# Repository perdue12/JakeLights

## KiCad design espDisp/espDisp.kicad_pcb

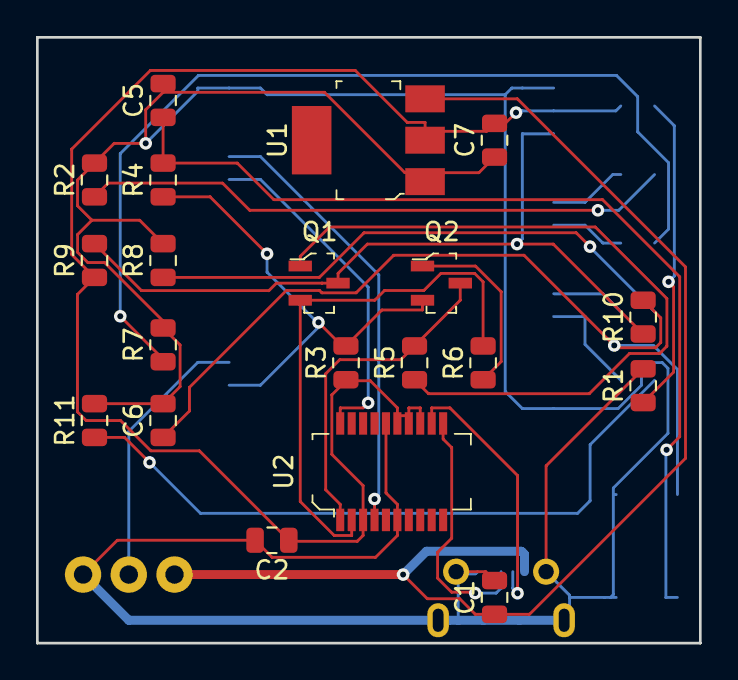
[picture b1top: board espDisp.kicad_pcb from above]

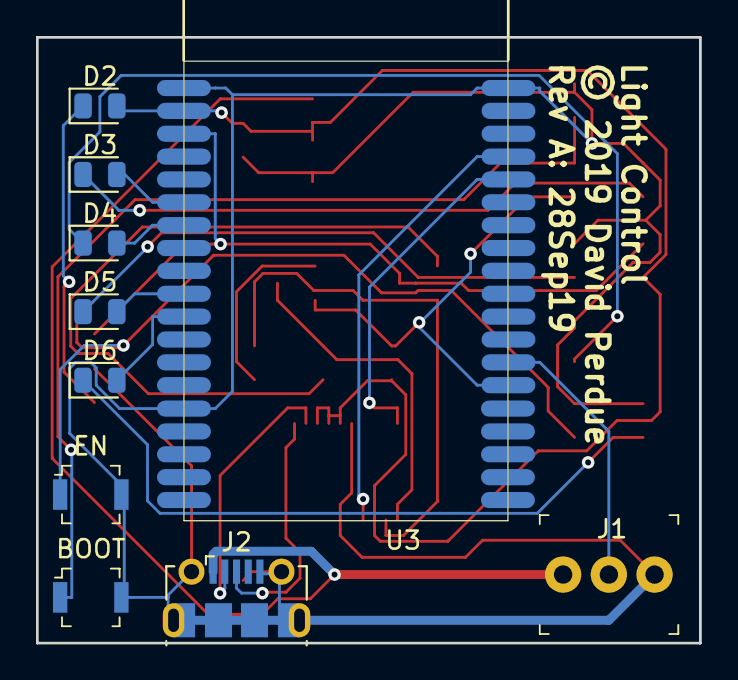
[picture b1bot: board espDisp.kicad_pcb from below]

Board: 2 copper layers, 36.8 x 33.7 mm, 30 parts (10 on the bottom side), 25 nets.

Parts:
BOOT: BOOT; Switch_Tactile_SMD_B3U-1000P
C1, C2, C5, C6: 1.0u; C_0805_2012Metric
C7: 47u; C_0805_2012Metric
D2, D3, D4, D5, D6: LED; LED_0805_2012Metric
EN: EN; Switch_Tactile_SMD_B3U-1000P
J1: 0022232031; PinHeader_1x3_P2.54mm_Drill1.02mm
J2: USB_B_Micro; USB_Micro-B_Molex-105017-0001
Q1, Q2: BC817-25-TP; SOT-23-3
R1, R2, R7, R8, R11: 200; R_0805_2012Metric
R3, R4, R9, R10: 1K; R_0805_2012Metric
R5, R6: 10K; R_0805_2012Metric
U1: AZ1117CH-3_3TRG1; SOT-223
U2: FT231XS-U; SSOP-20_W3.9mm
U3: ESP32-WROVER

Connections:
340RX: U2.4, U3.35
340TX: U2.20, U3.34
+3V3: C2.1, C7.2, D2.2, R3.1, R9.1, U1.2, U2.3, U2.13, U2.14, U2.15, U3.2
+5V: C1.1, J1.1, J2.1, U1.3
DTR: Q2.3, R5.2, U2.1
EN: Q1.3, R9.2, R10.1, U3.3
GND: BOOT.2, C1.2, C2.2, C5.2, C6.2, C7.1, EN.2, J1.3, J2.5, J2.6, R1.2, R2.2, R7.2, R8.2, R11.2, U1.1, U2.6, U2.16, U3.1, U3.15, U3.38
IO0: Q2.2, R3.2, R4.1, U3.25
LED1: D3.2, U3.6
LED2: D4.2, U3.7
LED3: D5.2, U3.10
LED4: D6.2, U3.11
LED_Din: J1.2, U3.26
unnamed: BOOT.1, C5.1, R4.2
unnamed: C6.1, EN.1, R10.2
unnamed: D2.1, R1.1
unnamed: D3.1, R2.1
unnamed: D4.1, R7.1
unnamed: D5.1, R8.1
unnamed: D6.1, R11.1
unnamed: Q1.1, R5.1
unnamed: Q2.1, R6.1
RTS: Q1.2, R6.2, U2.2
USB_D+: J2.3, U2.11
USB_D-: J2.2, U2.12

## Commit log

2019-08-18 Initlal commit
2019-08-18 before trying json
2019-08-18 reflashing
2019-08-18 fixed readme
2019-08-19 About to go asyncio
2019-08-25 add spiram
2019-08-25 seperated main and boot
2019-08-25 Don't redefin the pins you are using for i2c comms
2019-08-25 added regex
2019-08-25 web api, and set light function working
2019-08-25 made led array 1 based.
2019-08-27 changed to proper logging
2019-08-28 added newer roms
2019-08-28 removed oled
2019-09-01 changed to tinyweb
2019-09-01 remove led from boot
2019-09-02 Working json and async
2019-09-02 removed some prints
2019-09-02 set dhcp hostname
2019-09-02 increased sleep between calls to np.write
2019-09-02 added index
2019-10-14 added pcb files
2019-10-14 add git ignore

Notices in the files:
espDisp/espDisp.kicad_pcb:
© 2019 David Perdue
